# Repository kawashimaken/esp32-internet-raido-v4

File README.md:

# esp32-internet-raido-v4

find kicad project files in [here](https://github.com/kawashimaken/esp32-internet-raido-v4/tree/main/hardware/kicad/esp32_internet_radio_v4)

I use KiCad 6.0.5 for this project.

* We can also use vertical pin socket for ENCODER. 

# Wemos D1 R32

This extension board is designed for this:
https://ja.aliexpress.com/item/1005001621901111.html

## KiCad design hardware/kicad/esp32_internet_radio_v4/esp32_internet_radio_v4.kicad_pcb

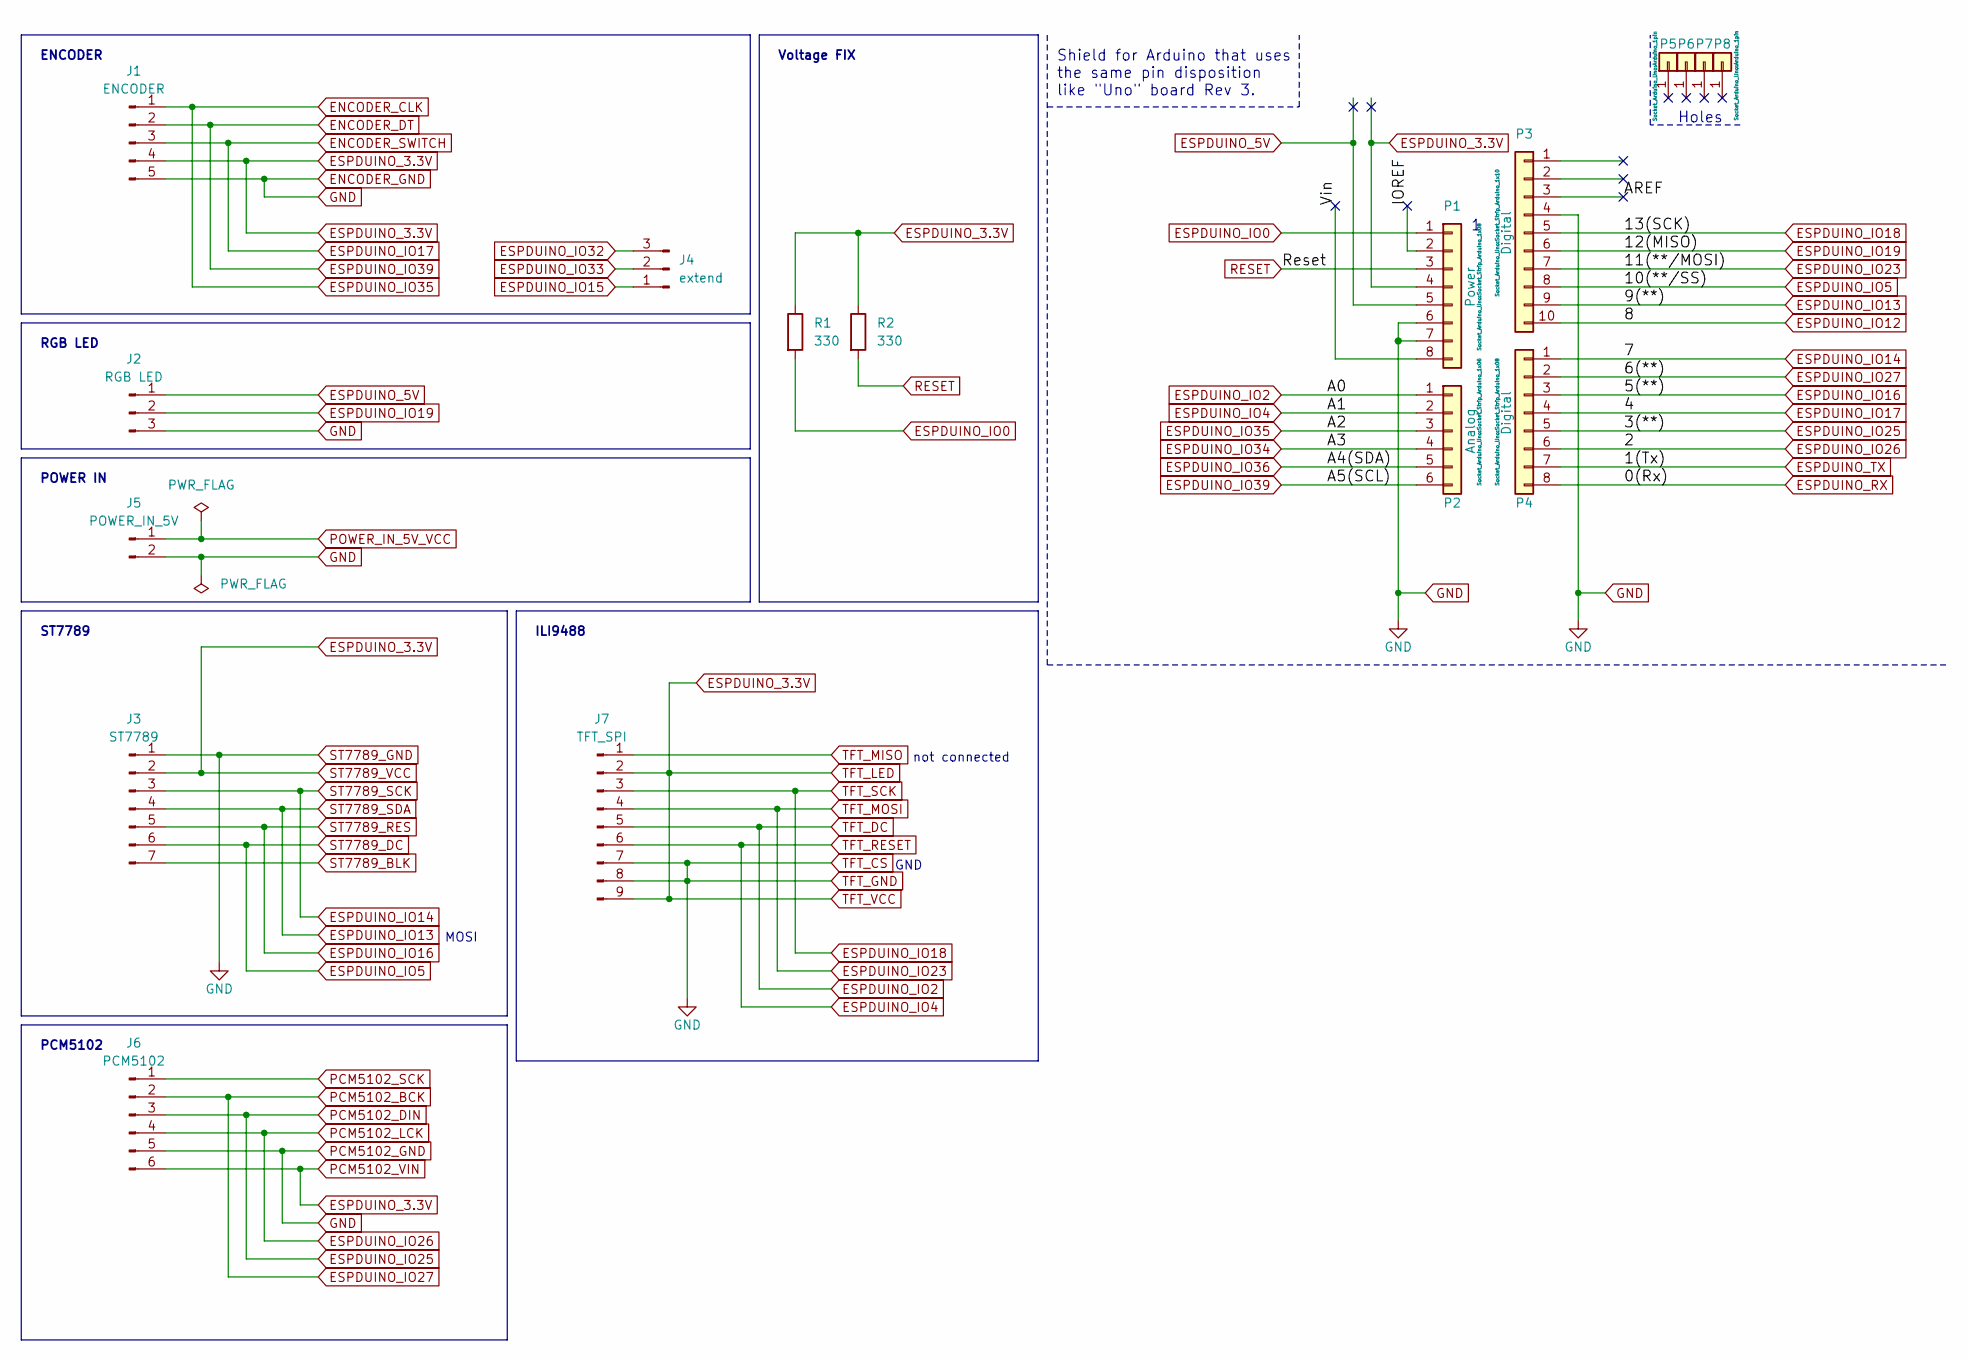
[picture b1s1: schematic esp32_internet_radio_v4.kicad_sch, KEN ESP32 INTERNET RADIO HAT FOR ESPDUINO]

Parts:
J1: ENCODER; PinHeader_1x05_P2.54mm_Vertical
J2: RGB LED; PinHeader_1x03_P2.54mm_Vertical
J3: ST7789; PinSocket_1x07_P2.54mm_Vertical
J4: extend; PinHeader_1x03_P2.54mm_Vertical
J5: POWER_IN_5V; PinHeader_1x02_P2.54mm_Vertical
J6: PCM5102; PinSocket_1x06_P2.54mm_Vertical
J7: TFT_SPI; PinHeader_1x09_P2.54mm_Vertical
P1: Power; Socket_Strip_Arduino_1x08
P2: Analog; Socket_Strip_Arduino_1x06
P3: Digital; Socket_Strip_Arduino_1x10
P4: Digital; Socket_Strip_Arduino_1x08
P5, P6, P7, P8: CONN_01X01; Arduino_1pin
R1, R2: 330; R_Axial_DIN0207_L6.3mm_D2.5mm_P10.16mm_Horizontal

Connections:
/AREF: P3.3
/IOREF: P1.2
/Vin: P1.8
ENCODER_CLK: J1.1, P2.3
ENCODER_DT: J1.2, P2.6
ENCODER_GND: J1.5, J2.3, J3.1, J5.2, J6.5, J7.7, J7.8, P1.6, P1.7, P3.4
ENCODER_SWITCH: J1.3, P4.4
ESPDUINO_3.3V: J1.4, J3.2, J6.6, J7.2, J7.9, P1.4, R1.1, R2.1
ESPDUINO_5V: J2.1, P1.5
ESPDUINO_IO0: P1.1, R1.2
ESPDUINO_IO2: J7.5, P2.1
ESPDUINO_IO4: J7.6, P2.2
ESPDUINO_IO5: J3.6, P3.8
ESPDUINO_IO12: P3.10
ESPDUINO_IO13: J3.4, P3.9
ESPDUINO_IO14: J3.3, P4.1
ESPDUINO_IO15: J4.1
ESPDUINO_IO16: J3.5, P4.3
ESPDUINO_IO18: J7.3, P3.5
ESPDUINO_IO19: J2.2, P3.6
ESPDUINO_IO23: J7.4, P3.7
ESPDUINO_IO25: J6.3, P4.5
ESPDUINO_IO26: J6.4, P4.6
ESPDUINO_IO27: J6.2, P4.2
ESPDUINO_IO32: J4.3
ESPDUINO_IO33: J4.2
ESPDUINO_IO34: P2.4
ESPDUINO_IO36: P2.5
ESPDUINO_RX: P4.8
ESPDUINO_TX: P4.7
PCM5102_SCK: J6.1
POWER_IN_5V_VCC: J5.1
RESET: P1.3, R2.2
ST7789_BLK: J3.7
TFT_MISO: J7.1

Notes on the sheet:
ST7789
ENCODER
POWER IN
ILI9488
GND
Holes
Shield for Arduino that uses the same pin disposition like "Uno" board Rev 3.
RGB LED
Voltage FIX
MOSI
PCM5102
not connected

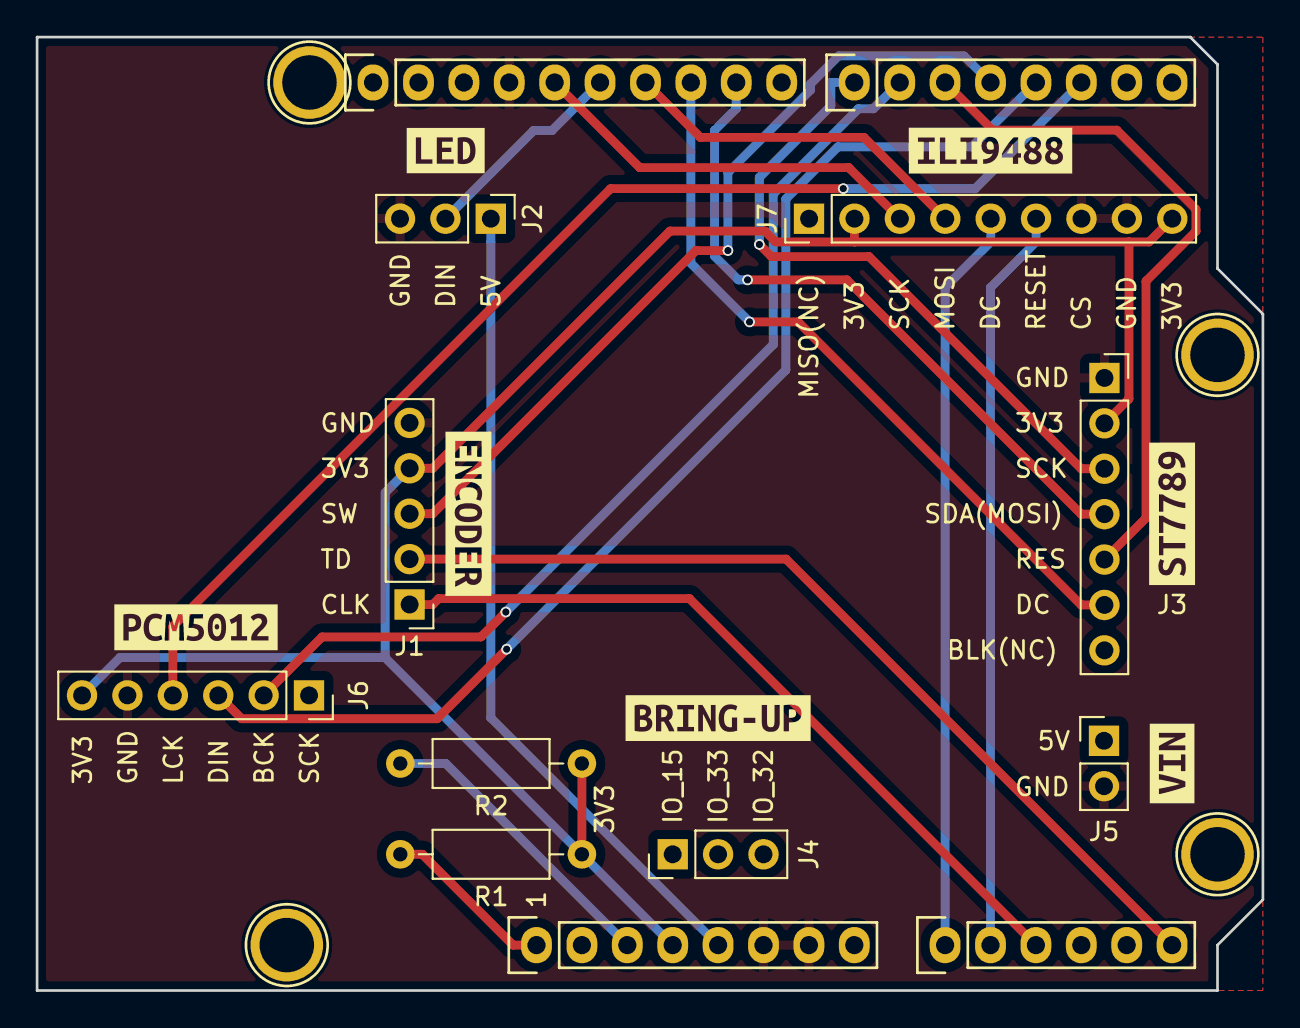
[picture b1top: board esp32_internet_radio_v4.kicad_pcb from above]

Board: 2 copper layers, 68.6 x 53.3 mm, 24 parts (0 on the bottom side), 20 nets.

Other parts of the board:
kibuzzard-6279C2B7: G***; kibuzzard-6279C2B7
kibuzzard-6279C2C8: G***; kibuzzard-6279C2C8
kibuzzard-6279C29F: G***; kibuzzard-6279C29F
kibuzzard-6279C31F: G***; kibuzzard-6279C31F
kibuzzard-6280E76A: G***; kibuzzard-6280E76A
kibuzzard-6280EDB6: G***; kibuzzard-6280EDB6
kibuzzard-6281B70A: G***; kibuzzard-6281B70A

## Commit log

2022-05-17 init commit
2022-05-17 update schematics
2022-05-20 update schematics (pinout)
2022-05-20 updated schematics and pcb
2022-05-20 update gerber files and pic
2022-05-20 update silk
2022-05-20 update zip file
2022-06-21 add svg
